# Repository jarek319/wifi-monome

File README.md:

# wifi-monome
A WiFi-enabled Controller

I really like those 4x4 squishy button pads used in Monomes.

Here's my attempt to make an open controller that can communicate over Wifi.

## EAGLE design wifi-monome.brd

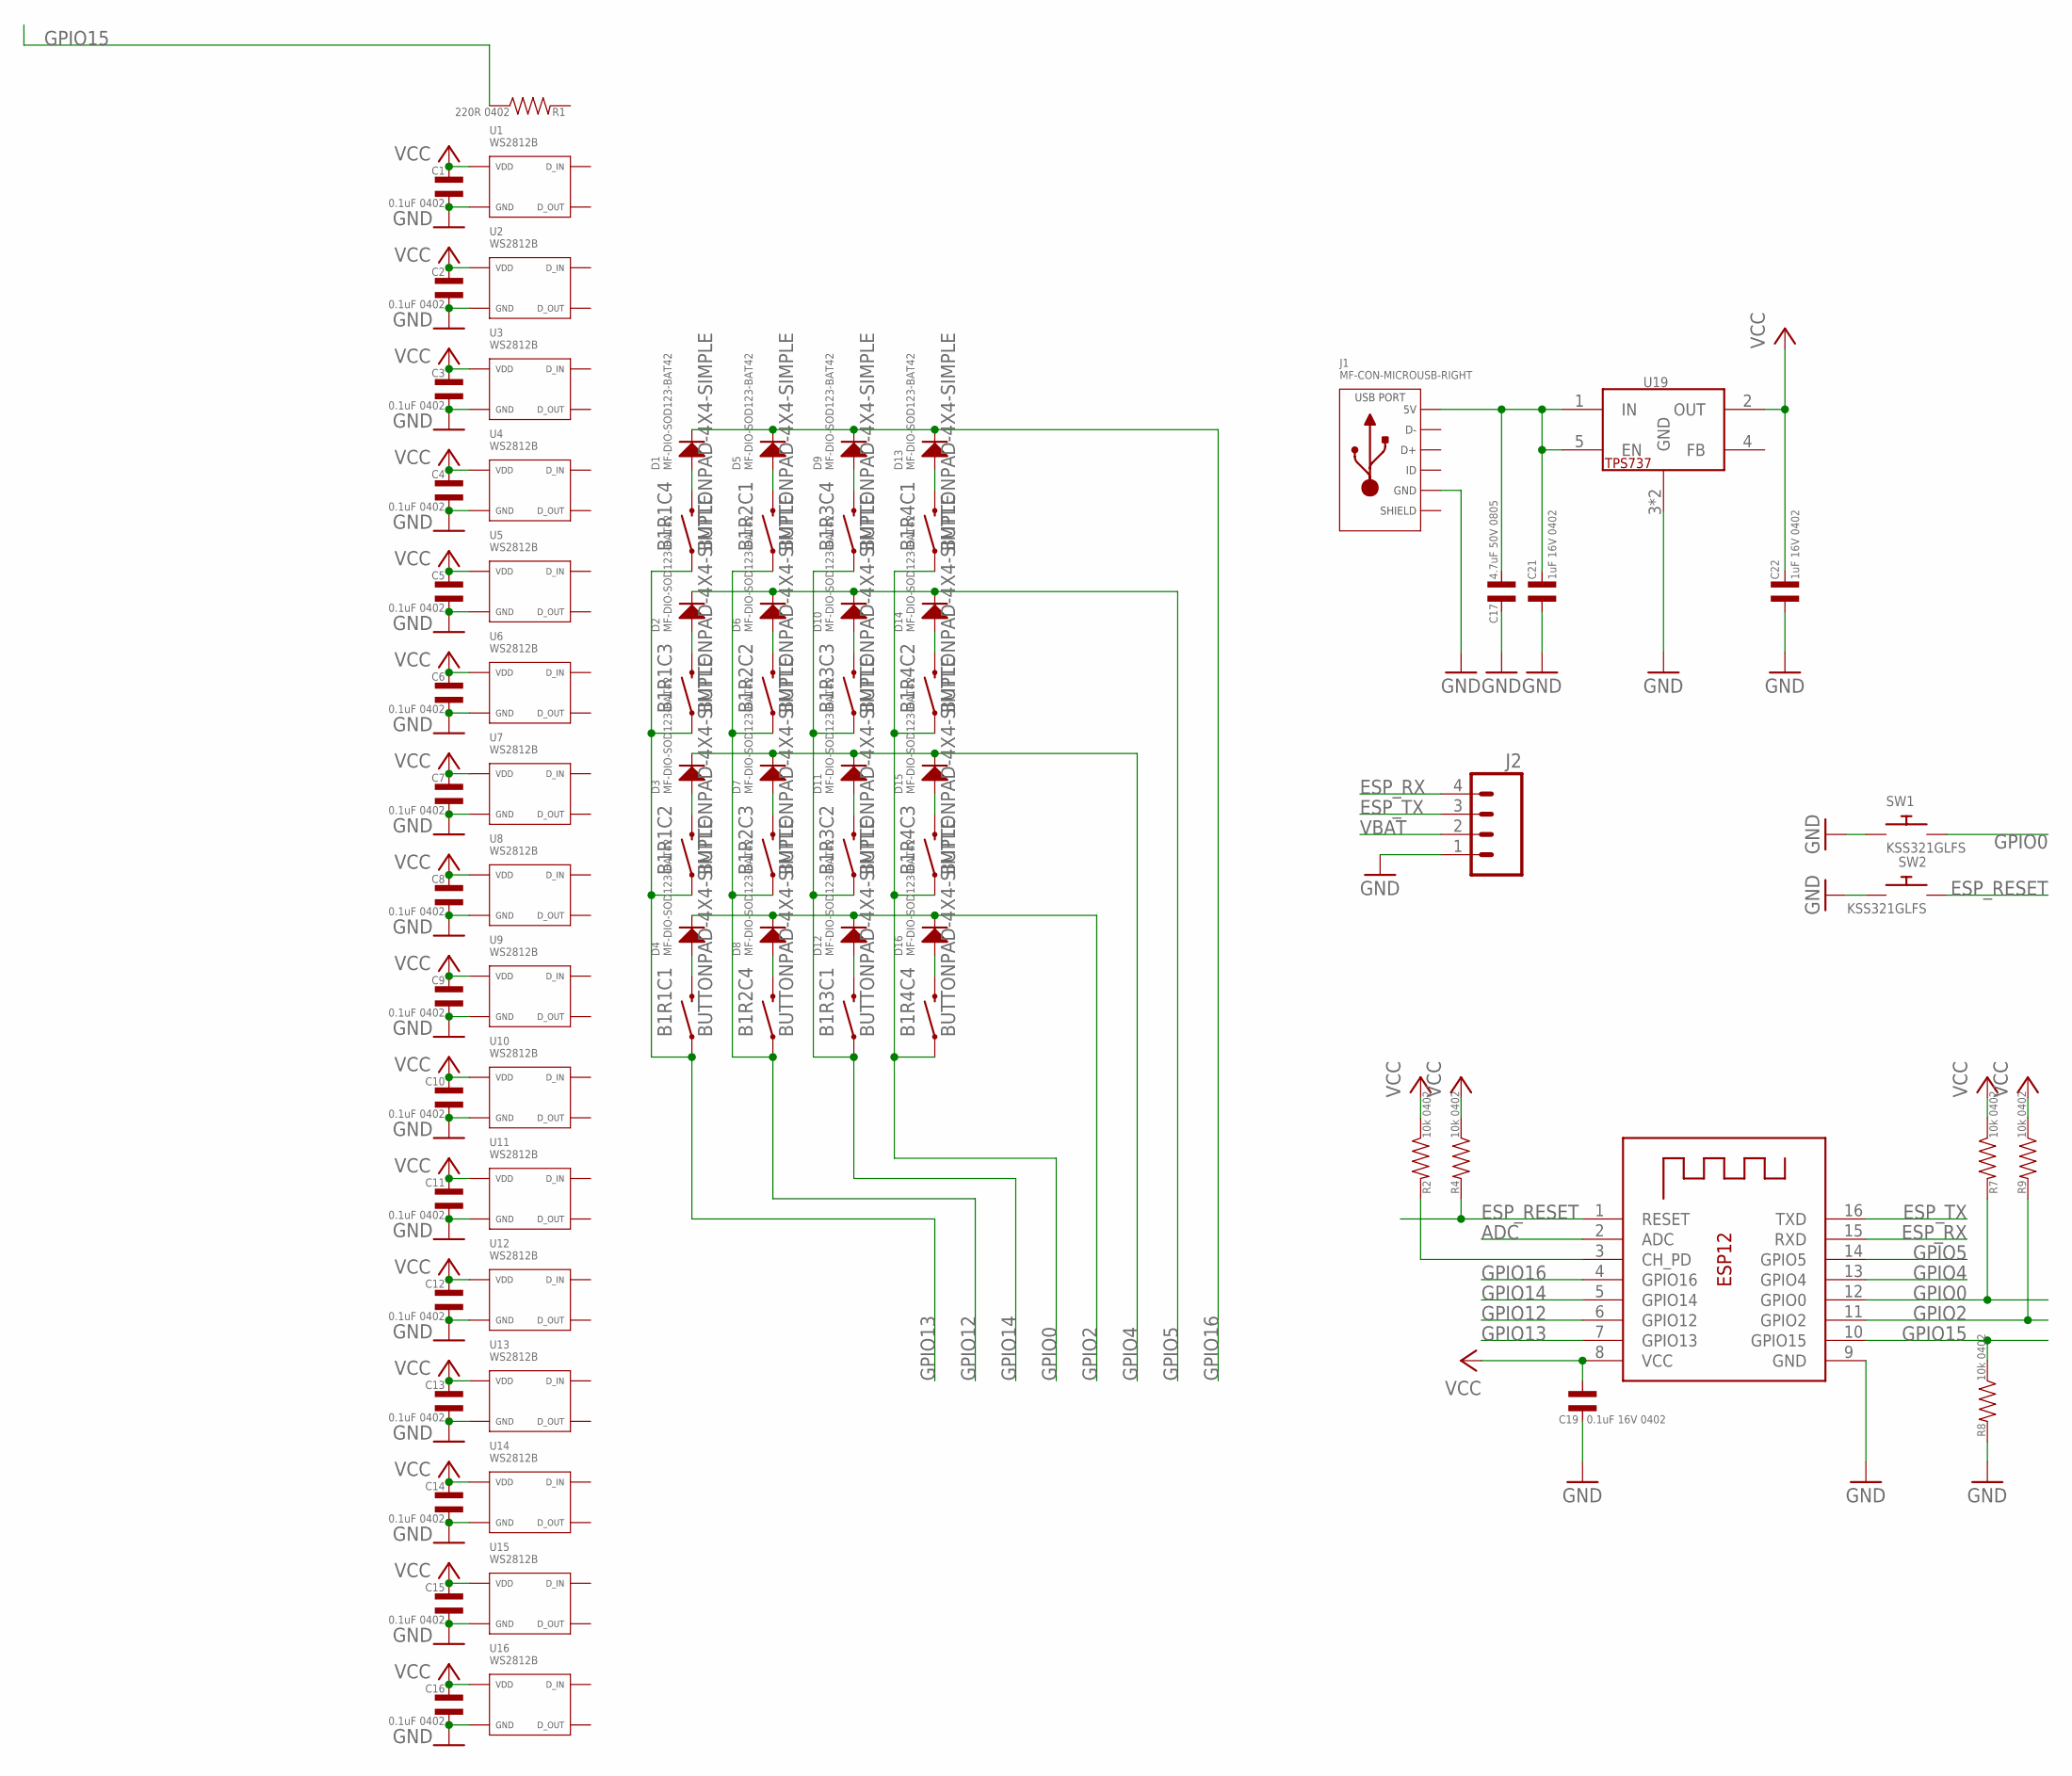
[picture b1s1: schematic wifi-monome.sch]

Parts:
B1: BUTTONPAD-4X4-SIMPLE
C1, C2, C3, C4, C5, C6, C7, C8, C9, C10, C11, C12, C13, C14, C15, C16: 0.1uF 0402; C0402
C17: 4.7uF 50V 0805; C0805
C19: 0.1uF 16V 0402; C0402
C21, C22: 1uF 16V 0402; C0402
D1, D2, D3, D4, D5, D6, D7, D8, D9, D10, D11, D12, D13, D14, D15, D16: MF-DIO-SOD123-BAT42; SOD-123
J1: MF-CON-MICROUSB-RIGHT; MICROUSB-RIGHT
J2: M04SMD_RA_FEMALE; 1X04_SMD_RA_FEMALE
R1: 220R 0402; R0402
R2, R4, R7, R8, R9: 10k 0402; R0402
SW1, SW2: KSS321GLFS; BTN_CK_KSS
U1, U2, U3, U4, U5, U6, U7, U8, U9, U10, U11, U12, U13, U14, U15, U16: WS2812B
U19: TPS73733DCQR; SOT223-6
X1: ESP-12e; ESP-12

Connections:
ADC: X1.2 (ADC)
ESP_RESET: R4.P$2, SW2.P$1, X1.1 (RESET)
ESP_RX: J2.4, X1.15 (RXD)
ESP_TX: J2.3, X1.16 (TXD)
GND: C1.P$2, C2.P$2, C3.P$2, C4.P$2, C5.P$2, C6.P$2, C7.P$2, C8.P$2, C9.P$2, C10.P$2, C11.P$2, C12.P$2, C13.P$2, C14.P$2, C15.P$2, C16.P$2, C17.P$2, C19.P$2, C21.P$2, C22.P$2, J1.5 (GND), J2.1, R8.P$2, SW1.P$1, SW2.P$2, U1.P$3 (VSS), U2.P$3 (VSS), U3.P$3 (VSS), U4.P$3 (VSS), U5.P$3 (VSS), U6.P$3 (VSS), U7.P$3 (VSS), U8.P$3 (VSS), U9.P$3 (VSS), U10.P$3 (VSS), U11.P$3 (VSS), U12.P$3 (VSS), U13.P$3 (VSS), U14.P$3 (VSS), U15.P$3 (VSS), U16.P$3 (VSS), U19.3 (GND), U19.6 (GND), X1.9 (GND)
GPIO0: B1.SIG24 (1), B1.SIG26 (1), B1.SIG28 (1), B1.SIG30 (1), R7.P$2, SW1.P$2, X1.12 (GPIO0)
GPIO2: D4.CATHODE, D8.CATHODE, D12.CATHODE, D16.CATHODE, R9.P$2, X1.11 (GPIO2)
GPIO4: D3.CATHODE, D7.CATHODE, D11.CATHODE, D15.CATHODE, X1.13 (GPIO4)
GPIO5: D2.CATHODE, D6.CATHODE, D10.CATHODE, D14.CATHODE, X1.14 (GPIO5)
GPIO12: B1.SIG8 (1), B1.SIG10 (1), B1.SIG12 (1), B1.SIG14 (1), X1.6 (GPIO12)
GPIO13: B1.SIG0 (1), B1.SIG2 (1), B1.SIG4 (1), B1.SIG6 (1), X1.7 (GPIO13)
GPIO14: B1.SIG16 (1), B1.SIG18 (1), B1.SIG20 (1), B1.SIG22 (1), X1.5 (GPIO14)
GPIO15: R1.P$1, R8.P$1, X1.10 (GPIO15)
GPIO16: D1.CATHODE, D5.CATHODE, D9.CATHODE, D13.CATHODE, X1.4 (GPIO16)
unnamed: B1.SIG3 (2), D3.ANODE
unnamed: B1.SIG1 (2), D4.ANODE
unnamed: C17.P$1, C21.P$1, J1.1 (5V), U19.1 (IN), U19.5 (EN)
unnamed: B1.SIG15 (2), D8.ANODE
unnamed: B1.SIG17 (2), D12.ANODE
unnamed: B1.SIG31 (2), D16.ANODE
unnamed: B1.SIG19 (2), D11.ANODE
unnamed: B1.SIG13 (2), D7.ANODE
unnamed: B1.SIG29 (2), D15.ANODE
unnamed: B1.SIG27 (2), D14.ANODE
unnamed: B1.SIG21 (2), D10.ANODE
unnamed: B1.SIG11 (2), D6.ANODE
unnamed: B1.SIG5 (2), D2.ANODE
unnamed: B1.SIG7 (2), D1.ANODE
unnamed: B1.SIG9 (2), D5.ANODE
unnamed: B1.SIG23 (2), D9.ANODE
unnamed: B1.SIG25 (2), D13.ANODE
unnamed: R2.P$2, X1.3 (CH_PD)
SLD: J1.S1 (SLD), J1.S2 (SLD), J1.S3 (SLD), J1.S4 (SLD), J1.S5 (SLD), J1.S6 (SLD)
VBAT: J2.2
VCC: C1.P$1, C2.P$1, C3.P$1, C4.P$1, C5.P$1, C6.P$1, C7.P$1, C8.P$1, C9.P$1, C10.P$1, C11.P$1, C12.P$1, C13.P$1, C14.P$1, C15.P$1, C16.P$1, C19.P$1, C22.P$1, R2.P$1, R4.P$1, R7.P$1, R9.P$1, U1.P$1 (VDD), U2.P$1 (VDD), U3.P$1 (VDD), U4.P$1 (VDD), U5.P$1 (VDD), U6.P$1 (VDD), U7.P$1 (VDD), U8.P$1 (VDD), U9.P$1 (VDD), U10.P$1 (VDD), U11.P$1 (VDD), U12.P$1 (VDD), U13.P$1 (VDD), U14.P$1 (VDD), U15.P$1 (VDD), U16.P$1 (VDD), U19.2 (OUT), X1.8 (VCC)

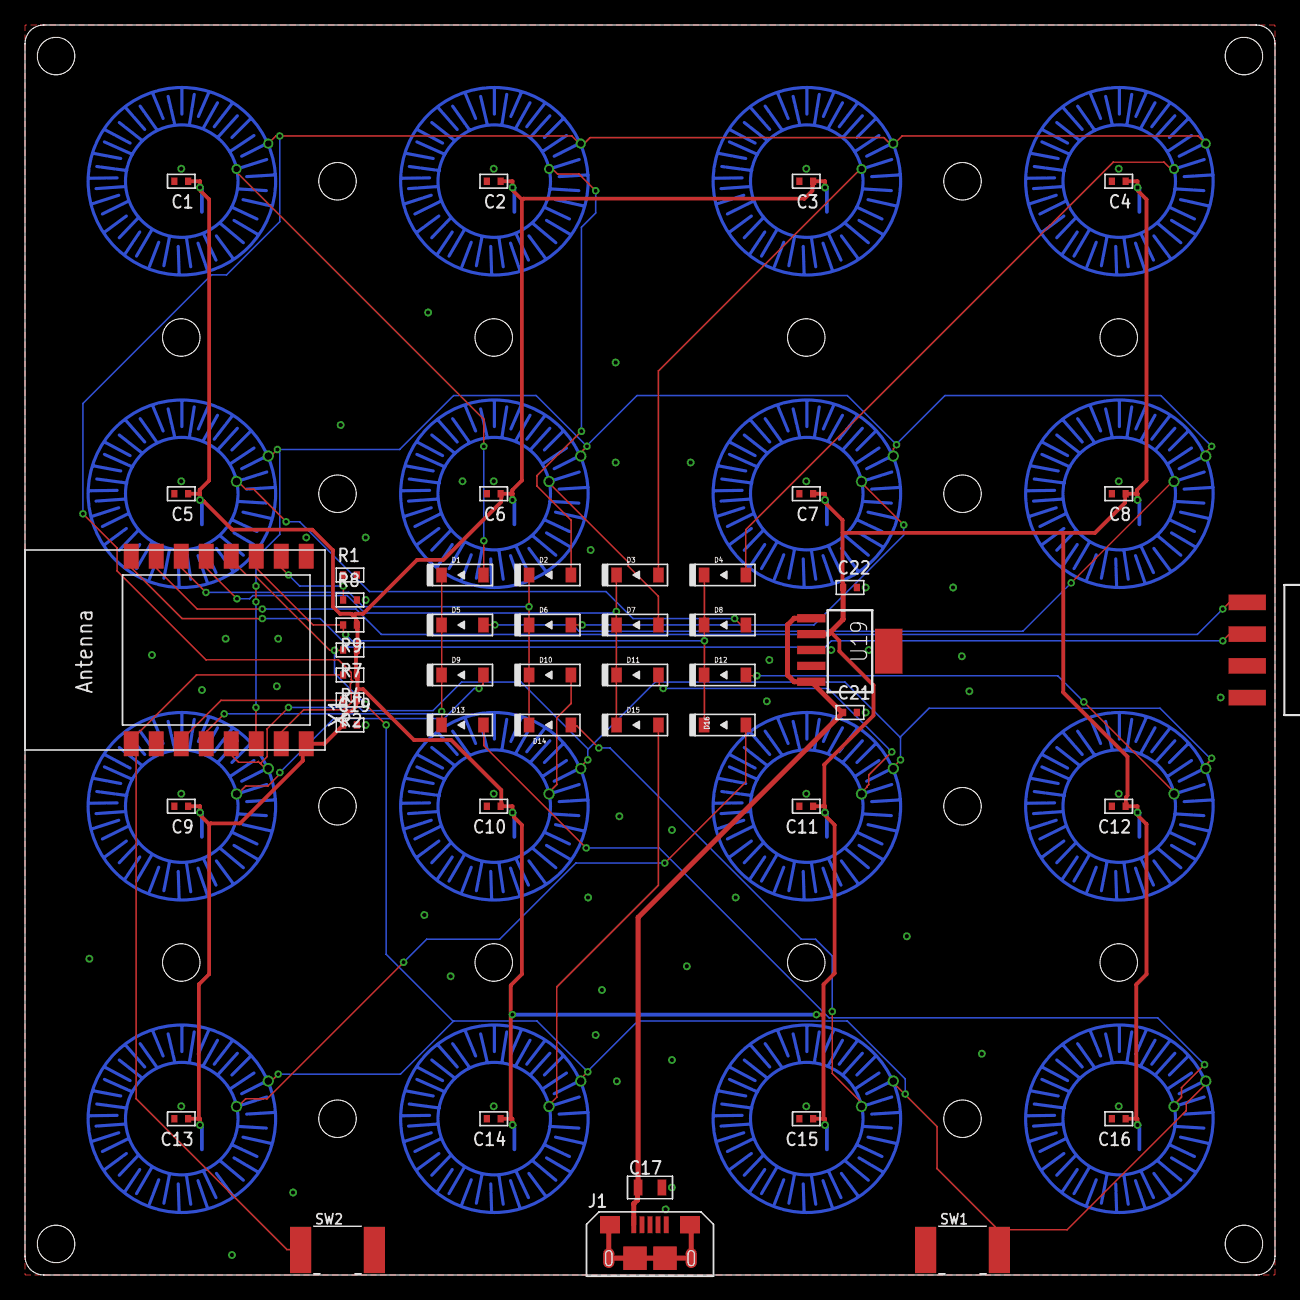
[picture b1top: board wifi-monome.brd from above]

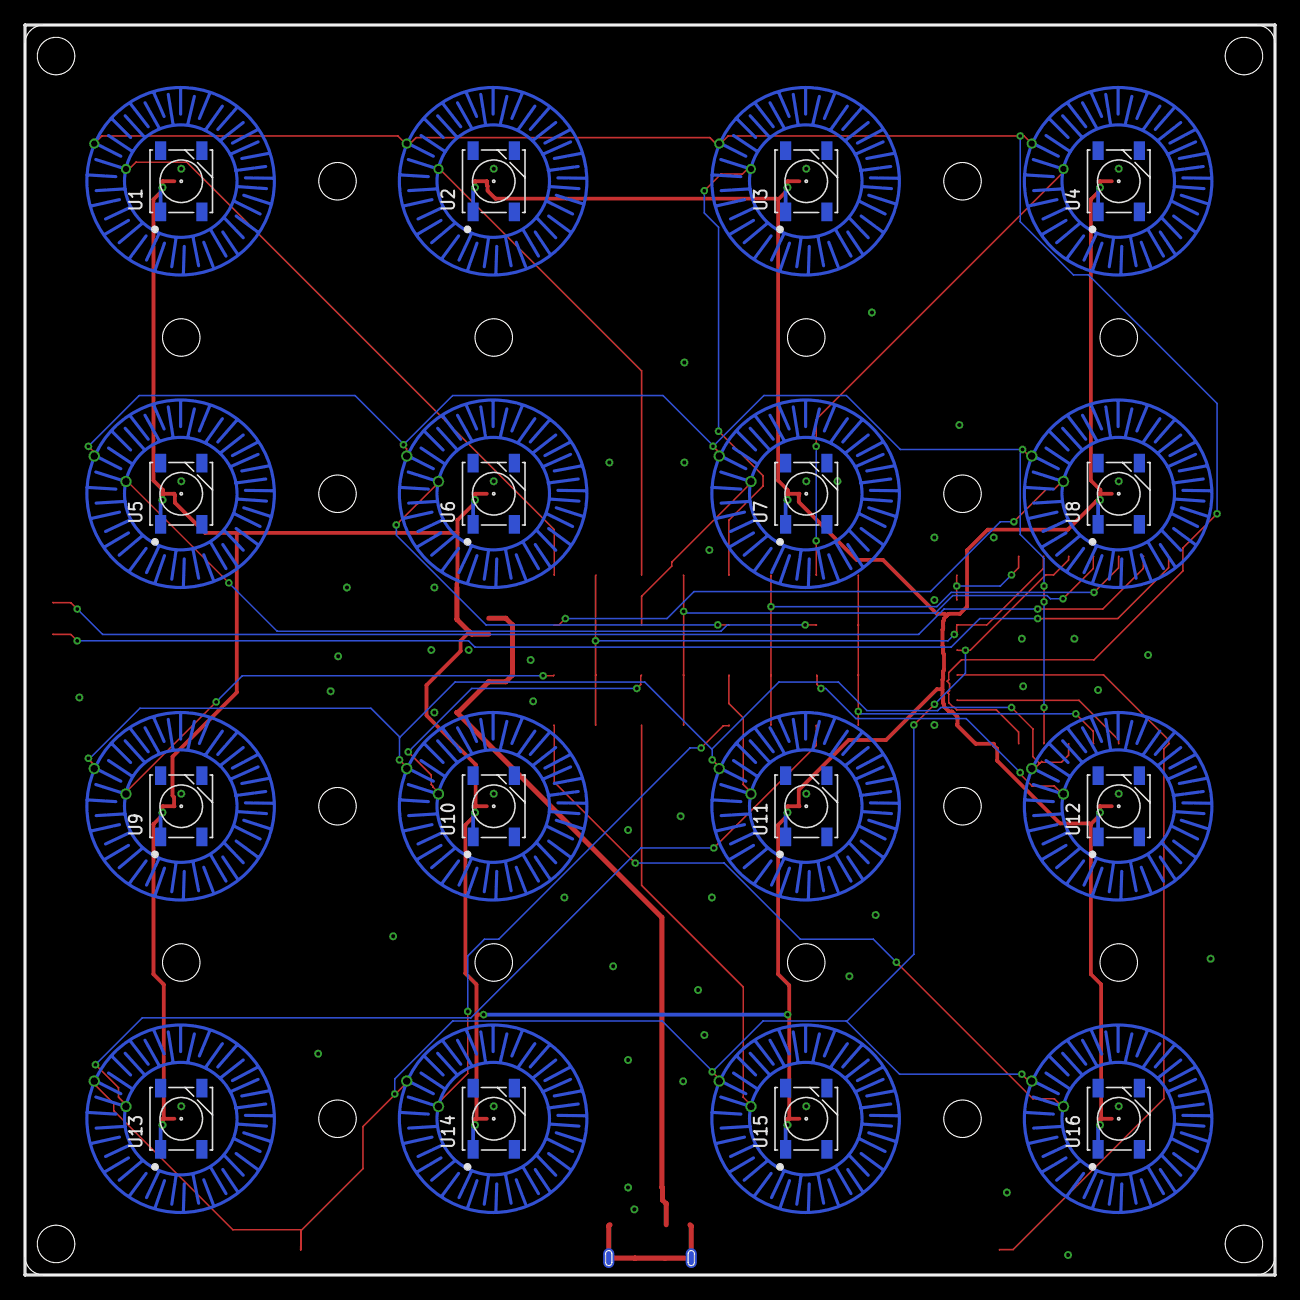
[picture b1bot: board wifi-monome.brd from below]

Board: 2 copper layers, 100.0 x 100.0 mm, 65 parts (17 on the bottom side), 33 nets.

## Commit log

2018-07-05 design prototyped: needs minor changes

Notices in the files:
parts and their libraries:
SparkFun-Connectors: Licensing: Creative Commons ShareAlike 4.0 International - https://creativecommons.org/licenses/by-sa/4.0
